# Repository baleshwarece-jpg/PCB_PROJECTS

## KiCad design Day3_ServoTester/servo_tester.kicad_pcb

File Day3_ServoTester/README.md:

# 🔧 Day 3 – Servo Tester PCB Design

## 📌 Project Overview

This project focuses on designing a **Servo Tester circuit on PCB**, which allows precise control of servo motor position using an analog input. The design emphasizes simplicity, stability, and practical implementation for embedded systems and robotics.

---

## ⚙️ Components Used

* Potentiometer (Position Control)
* Resistors (Biasing & Current Limiting)
* Capacitor (Noise Filtering / Stability)
* LED (Status Indication)
* Diode (1N4148 – Protection / Signal Conditioning)
* Connectors (Input/Output Interface)

---

## 🧠 Working Principle

The potentiometer acts as a variable input device, generating an analog voltage corresponding to the desired servo position.

This signal is conditioned using passive components (resistors and capacitors) to ensure stable operation. The circuit helps generate a control signal suitable for driving a servo motor (PWM-based control in practical implementations).

The LED provides visual feedback, and the diode ensures protection against reverse polarity or transient conditions.

---

## 🔑 Key Functionalities

* Manual control of servo position
* Stable signal conditioning using passive components
* Visual status indication using LED
* Protection using diode
* Compact and efficient PCB layout

---

## 🛠️ PCB Design Highlights

* Clean and minimal routing
* Proper component spacing for real-world assembly
* Noise reduction using capacitor placement
* Reliable connector placement for easy interfacing

---

## 🚀 Applications

* Robotics (servo control systems)
* Embedded systems testing
* Educational electronics projects
* Prototype development for motion control

---

## 📈 Future Enhancements

* Integration of microcontroller for precise PWM generation
* Digital display for angle indication
* Multi-servo control expansion
* Improved filtering for high precision applications

---

## 📷 Project Preview

---

## 🏁 Conclusion

This project strengthens understanding of **analog control interfacing, signal conditioning, and PCB design fundamentals**, forming a strong base for advanced embedded and robotics systems.

---

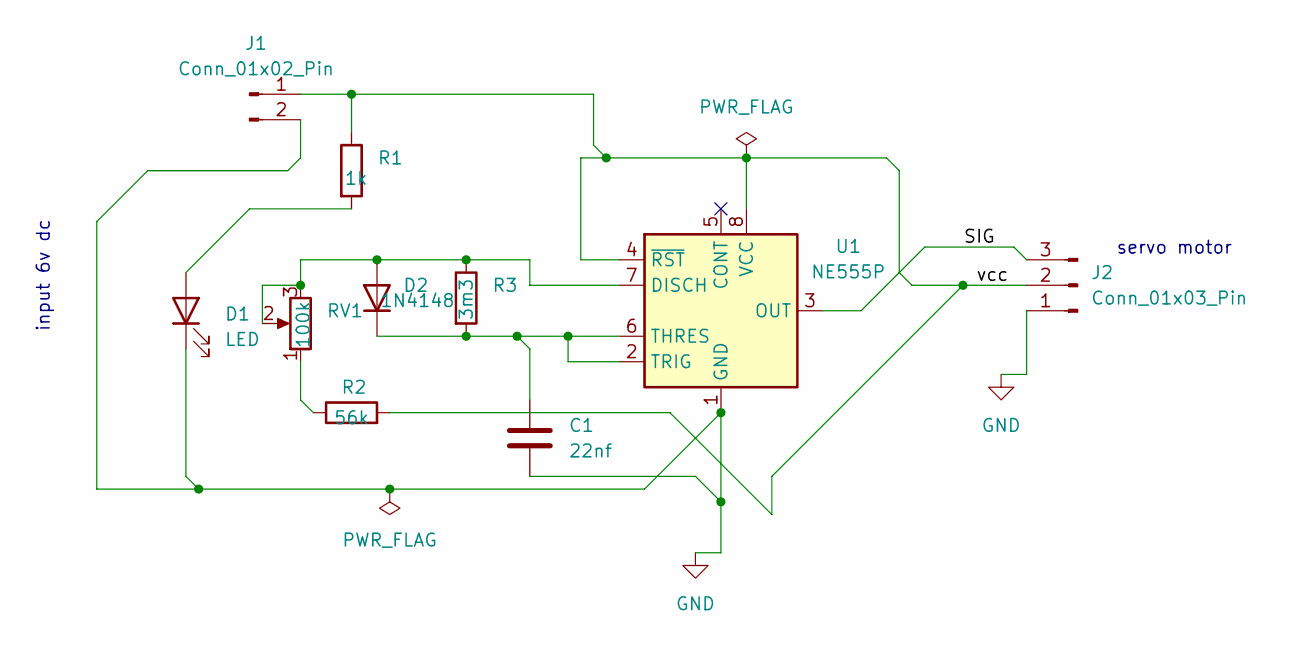
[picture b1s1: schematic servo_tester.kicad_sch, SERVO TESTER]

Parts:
C1: 22nf; C_Disc_D4.3mm_W1.9mm_P5.00mm
D1: LED; LED_D3.0mm
D2: 1N4148; D_DO-35_SOD27_P7.62mm_Horizontal
J1: Conn_01x02_Pin; PinHeader_1x02_P2.54mm_Vertical
J2: Conn_01x03_Pin; PinHeader_1x03_P2.54mm_Vertical
R1: 1k; R_Axial_DIN0204_L3.6mm_D1.6mm_P5.08mm_Horizontal
R2: 56k; R_Axial_DIN0204_L3.6mm_D1.6mm_P5.08mm_Horizontal
R3: 3m3; R_Axial_DIN0204_L3.6mm_D1.6mm_P5.08mm_Horizontal
RV1: 100k; Potentiometer_Alps_RK163_Single_Horizontal
U1: NE555P; DIP-8_W7.62mm

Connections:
/SIG: J2.3, U1.3 (OUT)
/vcc: J1.1, J2.2, R1.1, R2.2, U1.4 (~RST), U1.8 (VCC)
GND: C1.2, D1.1 (K), J1.2, J2.1, U1.1 (GND)
unnamed: D1.2 (A), R1.2
unnamed: D2.2 (A), R3.1, RV1.2, RV1.3, U1.7 (DISCH)
unnamed: C1.1, D2.1 (K), R3.2, U1.2 (TRIG), U1.6 (THRES)
unnamed: R2.1, RV1.1

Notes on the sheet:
servo motor
input 6v dc

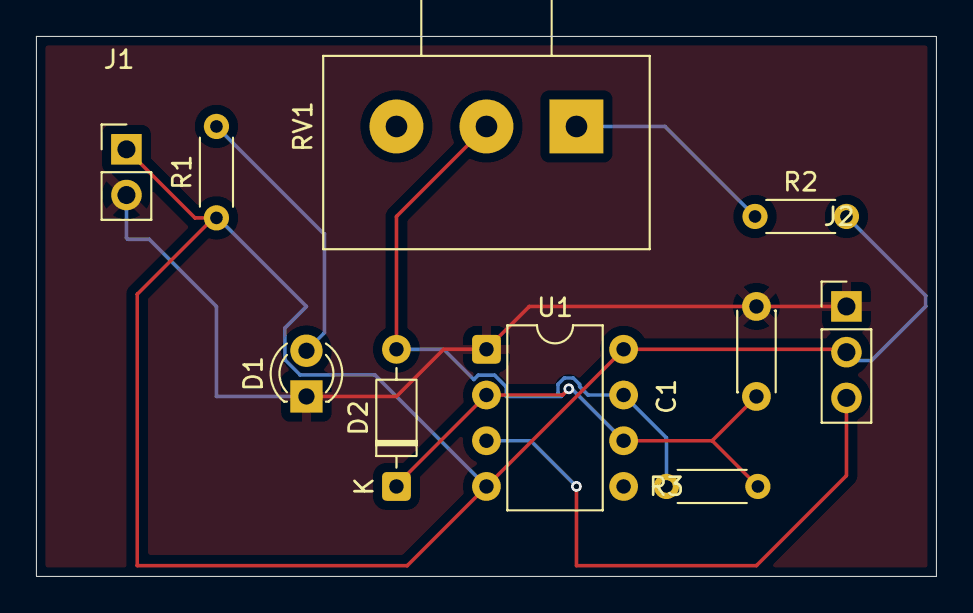
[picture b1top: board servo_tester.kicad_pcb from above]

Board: 2 copper layers, 50.0 x 30.0 mm, 10 parts (0 on the bottom side), 7 nets.

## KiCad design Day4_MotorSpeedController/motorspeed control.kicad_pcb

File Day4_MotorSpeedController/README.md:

## 📌 Day 4 – PCB Design Challenge

### 🔧 Project: Motor Speed Control Circuit

### 🧩 Components Used

* NE555P Timer IC
* TIP122 Transistor
* Diode (1N4007)
* Capacitor
* Resistor
* LED
* Screw Terminals

### ⚙️ Key Functionalities

* Generates PWM signal for motor speed variation
* Adjustable motor speed control
* TIP122 handles higher motor current
* LED indicates power/status
* Protection diode prevents back EMF damage

### 📘 Project Description

This project focuses on designing a motor speed control PCB using the NE555 timer IC for PWM generation. By adjusting the control input, the duty cycle changes, allowing smooth variation of DC motor speed. The TIP122 transistor acts as the driving stage for handling motor load efficiently. This project helped in understanding PWM-based motor control and practical PCB routing techniques.

### 🌍 Applications

* DC motor speed control
* Robotics projects
* Automation systems
* Mini cooling fans and DIY electronics

### 🚀 Future Improvements

* Add microcontroller-based smart control
* Include display for RPM monitoring
* MOSFET-based high-efficiency driver stage
* Compact SMD PCB version

### 📂 Repository Contents

## 📸 Project Visuals

### 🔹 Schematic

### 🔹 PCB Layout

### 🔹 3D View

💡 *Learning Focus:* PWM motor control, power transistor interfacing, and efficient PCB component placement.

---

#PCB #Electronics #HardwareDesign #EmbeddedSystems #MotorControl #Engineering #GitHubProjects

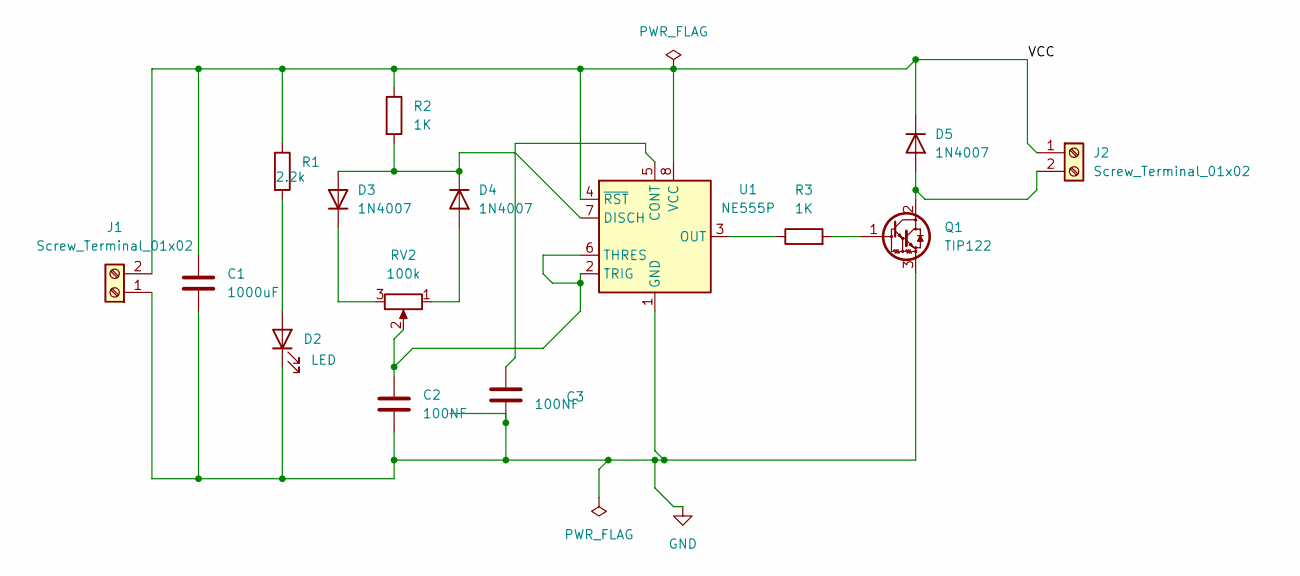
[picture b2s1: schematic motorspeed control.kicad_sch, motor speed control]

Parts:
C1: 1000uF; CP_Radial_D10.0mm_P5.00mm
C2, C3: 100NF; C_Disc_D4.7mm_W2.5mm_P5.00mm
D2: LED; LED_D5.0mm
D3, D4, D5: 1N4007; D_DO-41_SOD81_P10.16mm_Horizontal
J1, J2: Screw_Terminal_01x02; TerminalBlock_MaiXu_MX126-5.0-02P_1x02_P5.00mm
Q1: TIP122; TO-220-3_Vertical
R1: 2.2k; R_Axial_DIN0207_L6.3mm_D2.5mm_P7.62mm_Horizontal
R2, R3: 1K; R_Axial_DIN0207_L6.3mm_D2.5mm_P15.24mm_Horizontal
RV2: 100k; Potentiometer_Alps_RK163_Single_Horizontal
U1: NE555P; DIP-8_W7.62mm

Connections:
/VCC: C1.1, D5.1 (K), J1.2, J2.1, R1.1, R2.1, U1.4 (~RST), U1.8 (VCC)
GND: C1.2, C2.2, C3.2, D2.1 (K), J1.1, Q1.3 (E), U1.1 (GND)
unnamed: D2.2 (A), R1.2
unnamed: D3.2 (A), D4.1 (K), R2.2, U1.7 (DISCH)
unnamed: D3.1 (K), RV2.3
unnamed: D4.2 (A), RV2.1
unnamed: D5.2 (A), J2.2, Q1.2 (C)
unnamed: Q1.1 (B), R3.2
unnamed: C3.1, U1.5 (CONT)
unnamed: R3.1, U1.3 (OUT)
unnamed: C2.1, RV2.2, U1.2 (TRIG), U1.6 (THRES)

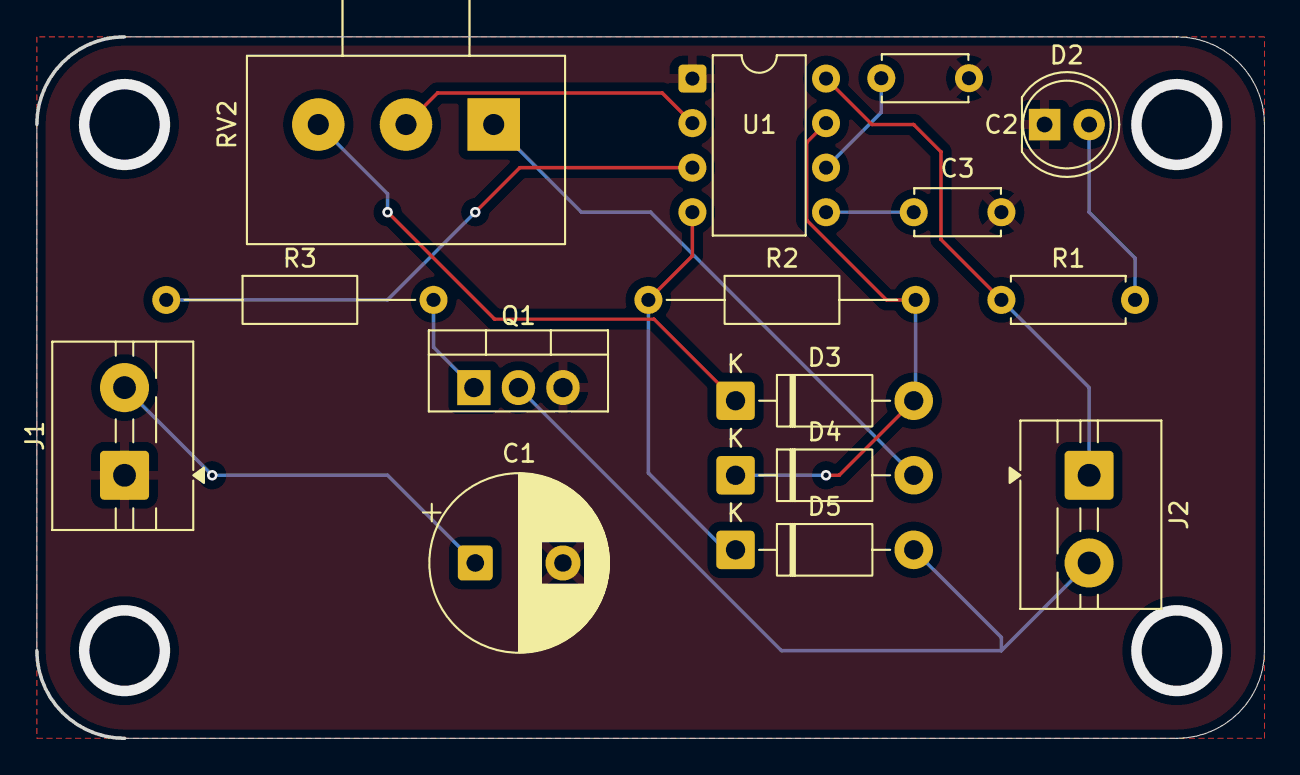
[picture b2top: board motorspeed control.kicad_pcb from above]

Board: 2 copper layers, 70.0 x 40.0 mm, 15 parts (0 on the bottom side), 11 nets.

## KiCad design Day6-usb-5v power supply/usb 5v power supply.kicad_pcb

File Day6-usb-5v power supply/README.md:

USB 5V Regulated Power Supply PCB 🔋⚡

A compact and reliable 5V regulated USB power supply PCB designed using the Advanced Monolithic Systems AMS1117-5.0 voltage regulator.
This project converts an external random DC input voltage into a stable 5V USB output suitable for powering embedded systems and electronics projects.

📌 Project Overview

The purpose of this project is to design a simple and efficient regulated power supply capable of delivering a constant 5V output through a USB connector.
The circuit uses the AMS1117 linear voltage regulator along with filtering capacitors to maintain voltage stability and reduce noise.

This PCB is beginner-friendly and useful for learning:

Voltage regulation
Power supply design
PCB layout fundamentals
USB power interfacing
Schematic-to-PCB workflow
🛠 Components Used
Component	Purpose
AMS1117-5.0	5V Voltage Regulation
USB-A Connector	5V Output Interface
DC Input Terminal	External Voltage Input
10µF Capacitors	Input/Output Filtering
100nF Capacitor	Noise Suppression
LED + Resistor	Power Indication
⚙️ Working Principle

The external DC supply is connected to the input terminal.
The AMS1117 regulator converts the varying input voltage into a stable 5V regulated output.

Power Flow:

External Input → AMS1117 Regulator → Filter Capacitors → USB 5V Output

The capacitors improve voltage stability and reduce ripple/noise in the output supply.

🔌 Features
Stable regulated 5V output
USB-powered output interface
Compact PCB layout
Simple and low-cost design
Easy to manufacture
Beginner-friendly hardware project
🚀 Applications
Arduino projects
ESP8266 / ESP32 power supply
Sensor modules
Embedded systems
DIY electronics
Portable prototyping supply
📂 Project Files
Schematic Design
PCB Layout
Gerber Files
3D PCB View
Bill of Materials (BOM)
🧠 Learning Outcomes
Understanding LDO voltage regulators
PCB routing techniques
USB power circuit design
Capacitor placement in power circuits
PCB manufacturing workflow
🖥 Designed Using
KiCad EDA
📸 Project Preview

📈 Future Improvements
Reverse polarity protection
DC barrel jack input
Current protection fuse
USB-C output support
Switching regulator version for higher efficiency
🏷 Tags

PCB Design KiCad AMS1117 USB Power Supply Electronics Embedded Systems Hardware Design

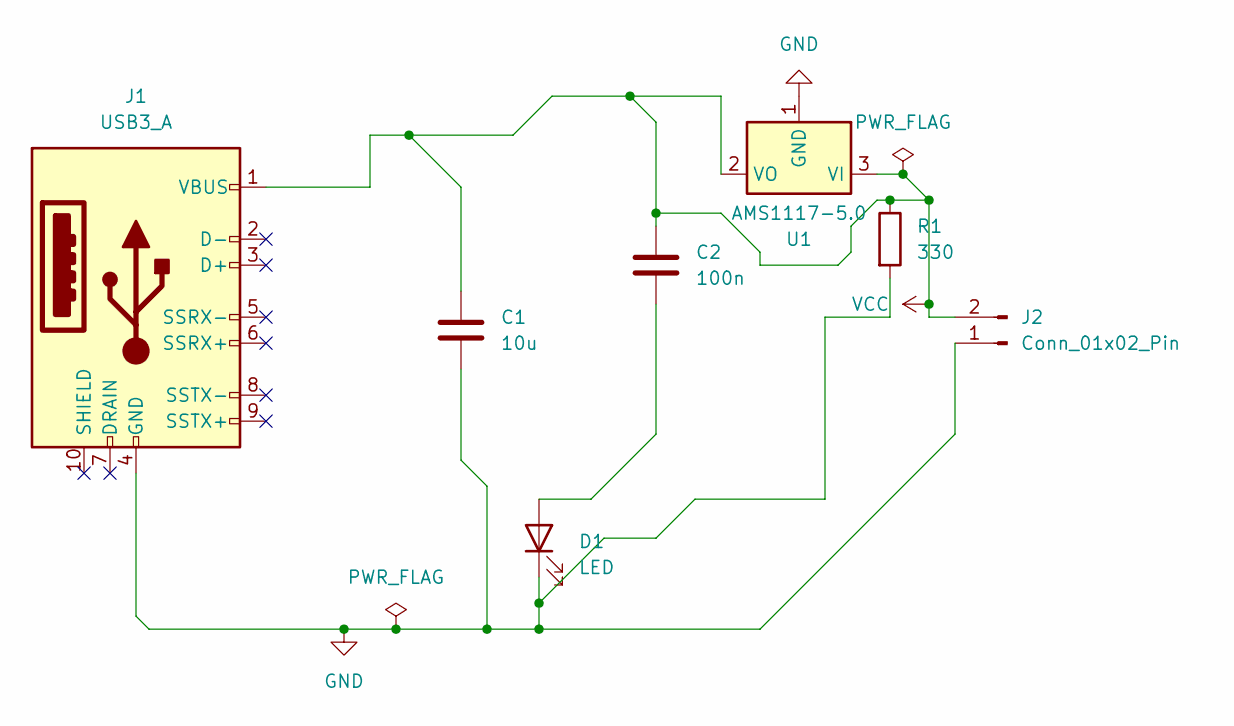
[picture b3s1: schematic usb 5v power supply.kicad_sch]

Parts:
C1: 10u; CP_Radial_D10.0mm_P2.50mm
C2: 100n; C_Disc_D7.5mm_W5.0mm_P10.00mm
D1: LED; LED_D4.0mm
J1: USB3_A; USB_A_CNCTech_1001-011-01101_Horizontal
J2: Conn_01x02_Pin; TerminalBlock_MaiXu_MX126-5.0-02P_1x02_P5.00mm
R1: 330; R_Axial_DIN0207_L6.3mm_D2.5mm_P10.16mm_Horizontal
U1: AMS1117-5.0; SOT-223-3_TabPin2

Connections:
GND: C1.1, D1.1 (K), J1.4 (GND), J2.1, R1.2, U1.1 (GND)
unnamed: C2.2, D1.2 (A)
VCC: C1.2, C2.1, J1.1 (VBUS), J2.2, R1.1, U1.2 (VO), U1.3 (VI)

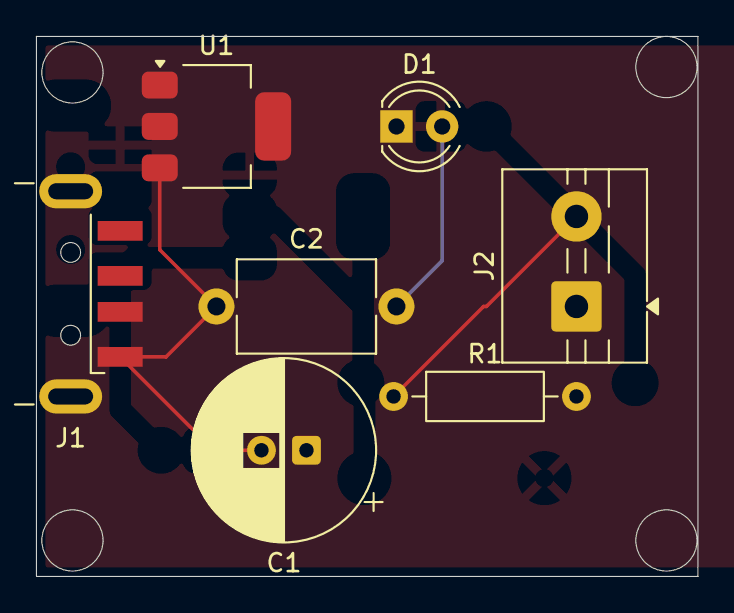
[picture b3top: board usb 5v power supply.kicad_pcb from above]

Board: 2 copper layers, 36.8 x 30.0 mm, 7 parts (0 on the bottom side), 3 nets.

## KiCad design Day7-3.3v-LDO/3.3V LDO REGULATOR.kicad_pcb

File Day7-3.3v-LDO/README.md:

🔌 3.3V LDO Voltage Regulator Board

Day 7 of the PCB Design Series — A compact, clean 3.3V regulated power supply board designed in KiCad using the AMS1117-3.3 LDO IC.

📋 Overview
This project is a minimal, reliable 3.3V Low Dropout (LDO) Voltage Regulator board that accepts an unregulated DC input (4V–12V) and outputs a stable 3.3V @ up to 800 mA — suitable for powering microcontrollers, sensors, and embedded modules such as ESP32, STM32, nRF52, and more.
Designed as part of a daily PCB design challenge series, this board demonstrates fundamental power supply design principles including bulk filtering, high-frequency decoupling, and thermal management.

⚡ Features

Input voltage: 4V – 12V DC
Output voltage: 3.3V (fixed)
Max output current: 800 mA
Dropout voltage: ~1.2V (at full load)
Input bulk capacitor: 100µF electrolytic (C1)
Input decoupling capacitor: 10µF MLCC ceramic (C2)
Output decoupling capacitor: 10µF MLCC ceramic (C3)
Output bulk capacitor: 100µF electrolytic (C4)
Optional power indicator: LED1 + R1 (1kΩ)
Connectors: 2-pin 2.54mm pitch headers (J1 input, J2 output)

🧩 Schematic

🛠️ KiCad Setup
Software: KiCad 7.x or later
Symbol libraries used:

Regulator_Linear:AMS1117-3.3
Device:C, Device:C_Polarized
Device:R, Device:LED
Connector_Generic:Conn_01x02

Footprint libraries used:

Package_TO_SOT_SMD:SOT-223-3_TabPin2
Capacitor_THT:CP_Radial_D6.3mm_P2.5mm
Capacitor_SMD:C_0805_2012Metric
Resistor_SMD:R_0805_2012Metric
LED_THT:LED_D3.0mm
Connector_PinHeader_2.54mm:PinHeader_1x02_P2.54mm_Vertical

📐 Design Notes

Capacitor placement: C2 and C3 (ceramic decoupling caps) must be placed as close as physically possible to U1's input and output pins on the PCB to maximize their high-frequency filtering effectiveness.
Thermal pad: The exposed tab (Pin 4) on the SOT-223 package connects to the VOUT net. Add a copper pour underneath and thermal vias to the bottom layer for effective heat dissipation at loads above 300 mA.
Dropout: Ensure VIN ≥ VOUT + 1.2V at all times. For a stable 3.3V output, supply at least 4.5V input.
LED: R1 limits LED current to ~3 mA at 3.3V. Reduce to 560Ω for ~5 mA if brighter indication is needed. The LED circuit is fully optional and can be omitted.

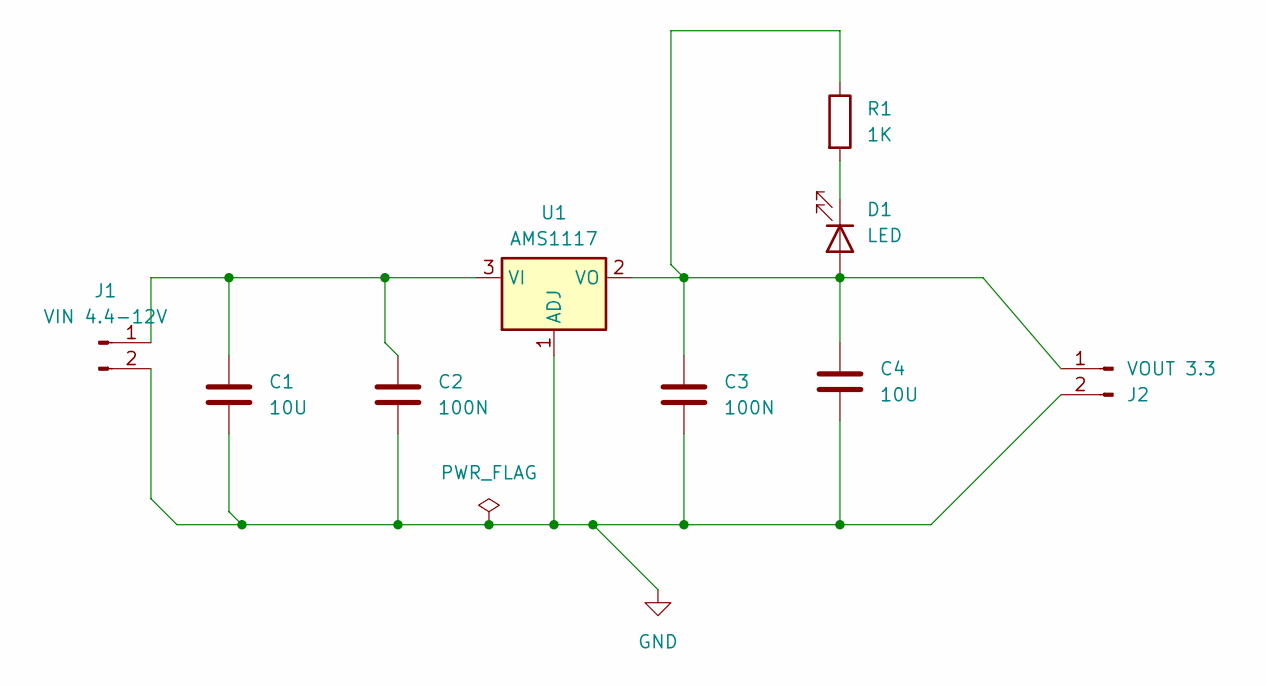
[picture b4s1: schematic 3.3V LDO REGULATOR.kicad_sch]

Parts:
C1: 10U; CP_Radial_D5.0mm_P2.50mm
C2, C3: 100N; C_0603_1608Metric
C4: 10U; CP_Radial_D5.0mm_P2.00mm
D1: LED; LED_D3.0mm
J1: VIN 4.4-12V; TerminalBlock_MaiXu_MX126-5.0-02P_1x02_P5.00mm
J2: VOUT 3.3; TerminalBlock_MaiXu_MX126-5.0-02P_1x02_P5.00mm
R1: 1K; R_0603_1608Metric
U1: AMS1117; SOT-223-3_TabPin2

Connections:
GND: C1.2, C2.2, C3.2, C4.2, J1.2, J2.2, U1.1 (ADJ)
unnamed: C3.1, C4.1, D1.2 (A), J2.1, R1.1, U1.2 (VO)
unnamed: D1.1 (K), R1.2
unnamed: C1.1, C2.1, J1.1, U1.3 (VI)

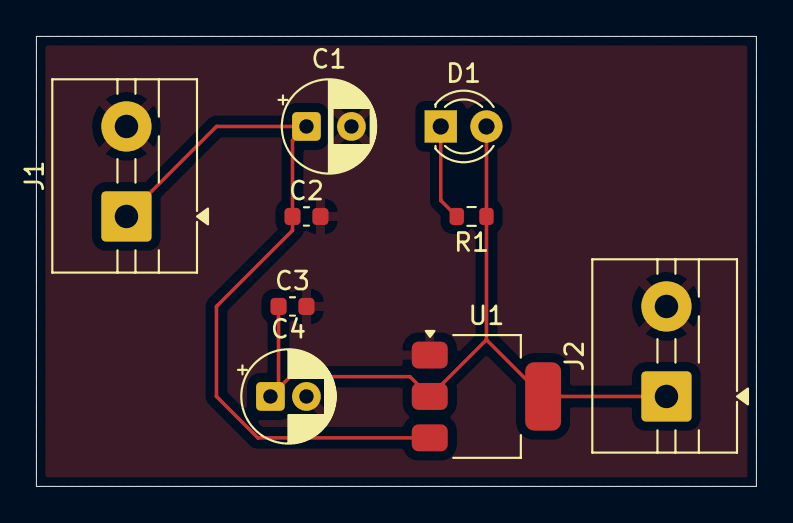
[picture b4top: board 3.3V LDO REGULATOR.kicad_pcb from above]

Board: 2 copper layers, 40.0 x 25.0 mm, 9 parts (0 on the bottom side), 4 nets.

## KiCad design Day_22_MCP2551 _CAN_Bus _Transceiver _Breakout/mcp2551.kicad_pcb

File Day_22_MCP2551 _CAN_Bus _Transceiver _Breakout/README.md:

# MCP2551 CAN Bus Transceiver Breakout
**Day 22 / 30 — 30-Day PCB Design Challenge**

A CAN bus transceiver breakout built around the MCP2551, converting a microcontroller's CAN controller TX/RX logic signals into differential CAN_H / CAN_L bus signaling. Designed for automotive, industrial, and embedded networking applications requiring robust multi-node communication.

---

## Overview

CAN (Controller Area Network) is a differential, multi-master serial bus designed for reliable communication in electrically noisy environments — originally developed for automotive use and now common in industrial automation, robotics, and embedded systems requiring deterministic, fault-tolerant networking. A CAN controller (either built into a microcontroller or implemented as a separate IC such as the MCP2515) handles the protocol logic and produces single-ended TX/RX signals. The MCP2551 transceiver sits between that controller and the physical bus, converting those logic-level signals into the differential CAN_H / CAN_L pair and providing the bus driver strength, common-mode range, and protection needed for real-world multi-node wiring.

This board exposes a clean TX/RX header for connection to any CAN controller, screw terminals for the bus pair, an onboard 120 ohm termination resistor with a selectable jumper, and bus protection appropriate for a transceiver expected to sit at the physical edge of a network.

---

## Specifications

| Parameter | Value |
|---|---|
| Supply Voltage | 4.5V – 5.5V (5V logic only — not 3.3V tolerant without level shifting) |
| Bus Standard | ISO 11898-2 (High-Speed CAN) |
| Max Bus Speed | 1 Mbps |
| Logic Interface | TXD, RXD (5V CMOS/TTL compatible) |
| Bus Connector | 2-pin screw terminal (CAN_H, CAN_L) |
| Termination | Onboard 120 ohm, jumper selectable |
| Bus Protection | TVS diode array on CAN_H/CAN_L |
| Slope Control | Resistor-set (RS pin), affects EMI and max bus speed |
| Standby Mode | Supported via RS pin pulled high |
| PCB | 2-layer, 1 oz copper |

---

## Why a Transceiver Breakout

A microcontroller's CAN peripheral — or an external CAN controller IC like the MCP2515 — only produces single-ended digital TX and RX signals referenced to the microcontroller's own ground. CAN bus signaling is differential by design specifically to reject common-mode noise across long cable runs and in electrically noisy environments such as vehicles or industrial equipment, where ground potential can vary meaningfully between nodes. Without a transceiver, the controller's logic-level signals cannot directly drive a CAN bus.

The MCP2551 was selected as a widely available, well-documented transceiver with a long track record in hobbyist and industrial designs, a 1 Mbps maximum data rate covering standard high-speed CAN applications, and built-in protection features (thermal shutdown, short-circuit protection on bus pins) suitable for a breakout board that may be wired into varied and sometimes imperfect bus environments during development.

---

## CAN Bus Topology Reminder

A CAN bus is wired as a linear topology with exactly two 120 ohm termination resistors, one at each physical end of the bus — not at every node.

```
Node A              Node B              Node C              Node D
(120R term)                                                 (120R term)
   |                   |                   |                   |
   +----CAN_H/CAN_L----+----CAN_H/CAN_L----+----CAN_H/CAN_L----+
```

Only the two end nodes should have termination enabled. Mid-bus nodes must leave their termination jumper open — incorrect termination (missing entirely, or enabled at every node) is one of the most common sources of CAN bus communication failures and is usually the first thing to check when a network will not communicate reliably.

---

## Schematic Overview

**U1 — MCP2551**
High-speed CAN transceiver. TXD input from the controller's CAN TX pin; RXD output to the controller's CAN RX pin. CAN_H and CAN_L outputs drive the differential bus pair. RS pin sets the transceiver's slope control mode — tied to GND through R1 for high-speed mode (steepest slew rate, used for this board's standard configuration), or pulled high for low-power standby mode where the transceiver only listens for bus activity.

**R1 — Slope Control Resistor (0 ohm / direct to GND)**
Configures the MCP2551 for high-speed operation with no slew rate limiting. For applications with longer bus lengths or stricter EMI requirements, this can be replaced with a resistor value per the MCP2551 datasheet's slope-control table to slow the output edge rate and reduce radiated emissions at the cost of maximum achievable bus speed.

**RT1 — Termination Resistor (120 ohm)**
Placed across CAN_H and CAN_L, in series with jumper JP1. Matches the characteristic impedance of standard CAN twisted-pair cable to prevent signal reflections at the bus ends.

**JP1 — Termination Enable Jumper**
Solder jumper or 2-pin header with shorting block. Bridge only if this board is physically located at one end of the bus. Leave open for any mid-bus node.

**D1 — Bidirectional TVS Diode Array**
Across CAN_H and CAN_L relative to GND, placed close to the bus screw terminal. Protects the MCP2551 bus pins from ESD events and transient voltage spikes coupled onto the bus wiring, which is a realistic exposure point since CAN cabling often runs through environments with switching inductive loads (relays, motors) on the same vehicle or installation.

**C1 — Supply Decoupling (100 nF)**
Placed directly at the MCP2551 VDD pin.

**C2 — Bulk Decoupling (10 µF)**
Local bulk capacitance on the 5V supply rail feeding the transceiver.

**J1 — Logic Header**
4-pin, 2.54 mm pitch: VCC, GND, TXD (input from controller), RXD (output to controller).

**J2 — Bus Terminal**
2-pin screw terminal, 5.08 mm pitch: CAN_H, CAN_L.

---

## PCB Design Notes

- Designed in **KiCad 8**
- CAN_H and CAN_L routed as a matched-length differential pair from the MCP2551 output pins to the screw terminal, keeping both traces equal length to preserve common-mode noise rejection
- Differential pair kept away from the logic-side TXD/RXD traces and any digital switching signals on the same board to avoid coupling noise onto the bus pair
- TVS diode placed as close to the bus screw terminal as the layout allows, intercepting transients before they reach the MCP2551
- Ground plane maintained beneath the differential pair for controlled impedance and return current path
- Termination resistor and jumper placed near the bus terminal, clearly silkscreened with "TERM" labeling and an open/closed indicator
- Logic-side and bus-side grounds are the same plane on this board (MCP2551 is not isolated) — for applications requiring galvanic isolation between the controller and bus, an isolated transceiver (e.g., MCP2562FD with an isolator, or a digital isolator ahead of a standard transceiver) would be required instead
- Silkscreen includes pinout labels for both headers and a bus wiring diagram reference

---

## Getting Started

### Wiring to a CAN Controller (e.g., MCP2515 SPI CAN Controller)

```
MCP2551 Breakout       CAN Controller (MCP2515)
─────────────────────────────────────────────────
VCC          ──────>   5V
GND          ──────>   GND
TXD          <──────   TXD (controller CAN TX output)
RXD          ──────>   RXD (controller CAN RX input)
```

### Wiring to a Microcontroller with Built-In CAN Peripheral (e.g., ESP32, STM32)

```
MCP2551 Breakout       Microcontroller
─────────────────────────────────────────────────
VCC          ──────>   5V (note: MCP2551 is not 3.3V logic compatible)
GND          ──────>   GND
TXD          <──────   CAN TX pin
RXD          ──────>   CAN RX pin
```

If the microcontroller's CAN peripheral operates at 3.3V logic, a level shifter is required between the controller and this board's TXD/RXD lines, since the MCP2551 requires a 5V logic-level interface and is not specified for direct 3.3V operation.

### Bus Wiring Between Multiple Nodes

```
                CAN_H ──────────────────────────── CAN_H
                CAN_L ──────────────────────────── CAN_L
   Node A (term ON)                                Node B (term ON)
                              |
                          Node C (term OFF, mid-bus)
```

Use twisted-pair cable for the CAN_H/CAN_L run. Keep stub lengths (the branch from the main bus to each node) as short as practical — long stubs introduce impedance discontinuities that degrade signal integrity at higher bus speeds.

### Arduino Example (using MCP2515 + this transceiver)

```cpp
#include <SPI.h>
#include <mcp2515.h>

MCP2515 mcp2515(10); // CS pin to MCP2515

struct can_frame canMsg;

void setup() {
  Serial.begin(115200);
  mcp2515.reset();
  mcp2515.setBitrate(CAN_500KBPS, MCP_8MHZ);
  mcp2515.setNormalMode();
}

void loop() {
  canMsg.can_id  = 0x036;
  canMsg.can_dlc = 4;
  canMsg.data[0] = 0x12;
  canMsg.data[1] = 0x34;
  canMsg.data[2] = 0x56;
  canMsg.data[3] = 0x78;
  mcp2515.sendMessage(&canMsg);
  delay(500);

  if (mcp2515.readMessage(&canMsg) == MCP2515::ERROR_OK) {
    Serial.print("ID: ");
    Serial.println(canMsg.can_id, HEX);
  }
}
```

Note that the MCP2515 in this example is the CAN controller (handling protocol and arbitration via SPI), and the MCP2551 on this breakout is the transceiver (handling the physical electrical signaling) — the two ICs serve distinct roles and both are required to put a microcontroller without native CAN hardware onto a bus.

---

## BOM

| Reference | Part | Package | Value / Part No. |
|---|---|---|---|
| U1 | MCP2551 | SOIC-8 | High-speed CAN transceiver |
| D1 | TVS diode array | SOT-23 | Bidirectional, bus protection |
| RT1 | Resistor | 0805 | 120 ohm, 1% (termination) |
| R1 | Resistor | 0402 | 0 ohm (slope control, direct to GND) |
| C1 | Ceramic | 0402 | 100 nF |
| C2 | Electrolytic / tantalum | 1206 | 10 µF |
| JP1 | Jumper / solder bridge | 2.54 mm, 2-pin | Termination enable |
| J1 | Pin header | 2.54 mm, 4-pin | VCC / GND / TXD / RXD |
| J2 | Screw terminal | 5.08 mm, 2-pin | CAN_H / CAN_L |

---

## Common Issues

**No communication between nodes**
Check termination first — exactly two nodes on the bus should have termination enabled (120 ohm each end), giving a measured resistance of approximately 60 ohm across CAN_H/CAN_L with the bus powered down. A reading near 120 ohm suggests only one terminator is active; a much lower reading suggests too many.

**Intermittent or corrupted messages at higher bus speeds**
Check stub lengths to each node and overall bus length against the bitrate being used — CAN bus length and maximum reliable bitrate are inversely related per the ISO 11898-2 specification. Long stubs are a common cause of speed-dependent reliability issues that do not appear at lower bitrates.

**RXD stuck high, no received traffic detected**
Verify TXD is not held low (which would dominate the bus and prevent normal arbitration), confirm the bus has correct termination, and check that CAN_H and CAN_L are not swapped at the screw terminal relative to other nodes on the same bus.

**Transceiver runs warm or enters thermal shutdown**
Usually indicates a bus short between CAN_H and CAN_L, or CAN_H/L shorted to VCC or GND. The MCP2551 has built-in short-circuit protection that will limit current, but sustained shorted conditions still generate heat. Check bus wiring for shorts before assuming the transceiver is faulty.

**Board will not communicate when connected to a 3.3V microcontroller directly**
The MCP2551 requires 5V logic levels on TXD and RXD. Direct connection from a 3.3V CAN peripheral output is below the MCP2551's input threshold for reliable operation. Use a logic-level shifter on TXD/RXD, or substitute a 3.3V-compatible transceiver if the application is fixed at 3.3V logic.

## Repository Structure

```
MCP2551-CAN-Breakout/
├── hardware/
│   ├── CAN_Transceiver.kicad_pro
│   ├── CAN_Transceiver.kicad_sch
│   ├── CAN_Transceiver.kicad_pcb
│   ├── gerbers/
│   │   └── CAN_Transceiver_gerbers.zip
│   └── bom/
│       └── CAN_Transceiver_BOM.csv
├── docs/
│   ├── schematic.pdf
│   ├── MCP2551_Datasheet.pdf
│   └── assembly_notes.md
└── README.md
```

---

## 30-Day PCB Challenge Progress

| Day | Board | Status |
|---|---|---|
| 20 | Discrete MOSFET H-Bridge Motor Driver | Complete |
| 21 | Low-Power Microphone Preamplifier (MAX4468) | Complete |
| **22** | **MCP2551 CAN Bus Transceiver Breakout** | **Complete** |
| 23 | Coming soon | — |

---

## License

Hardware design files released under **CERN OHL v2 — Permissive**.

---

## References

- [MCP2551 Datasheet — Microchip](https://ww1.microchip.com/downloads/en/DeviceDoc/20001667G.pdf)
- [MCP2515 Datasheet — Microchip](https://ww1.microchip.com/downloads/en/DeviceDoc/MCP2515-Stand-Alone-CAN-Controller-with-SPI-20001801J.pdf)
- [ISO 11898-2 — High-Speed CAN Physical Layer Standard](https://www.iso.org/standard/63648.html)
- [KiCad EDA](https://www.kicad.org/)

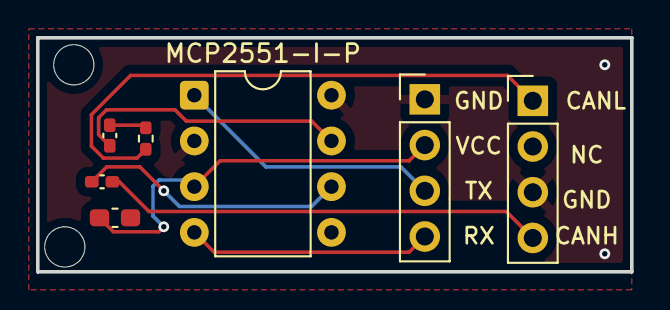
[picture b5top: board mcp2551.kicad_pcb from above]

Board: 2 copper layers, 33.0 x 13.0 mm, 7 parts (0 on the bottom side), 9 nets.

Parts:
C1: C; C_0603_1608Metric_Pad1.08x0.95mm_HandSolder
FB1, FB3: FerriteBead; L_0402_1005Metric_Pad0.77x0.64mm_HandSolder
J3: Conn_01x04_Pin; PinHeader_1x04_P2.54mm_Vertical
MCP2551-I-P: MCP2551-I-P; DIP-8_W7.62mm
R1: R; R_0402_1005Metric_Pad0.72x0.64mm_HandSolder
VCC: Conn_01x04_Pin; PinHeader_1x04_P2.54mm_Vertical

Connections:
/CANH: FB3.2, J3.4
/GND: C1.2, J3.3, MCP2551-I-P.2 (VSS), MCP2551-I-P.5 (Vref), MCP2551-I-P.8 (Rs), VCC.1
/RX: MCP2551-I-P.4 (RXD), VCC.4
/TX: MCP2551-I-P.1 (TXD), VCC.3
/VCC: C1.1, MCP2551-I-P.3 (VDD), VCC.2
/canl: J3.1, R1.1
unnamed: FB1.2, R1.2
unnamed: FB1.1, MCP2551-I-P.7 (CANH)
unnamed: FB3.1, MCP2551-I-P.6 (CANL)
